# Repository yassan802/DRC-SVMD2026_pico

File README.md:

マイコンにRP2354Aを用いたサーボモータドライバ基板。  
主な従来のものとの変更点はマイコンの変更、チャンネル数が6chになったこと、
リミットスイッチ用端子を新しく付けたこと、サーボ用端子をxhにしたこと。

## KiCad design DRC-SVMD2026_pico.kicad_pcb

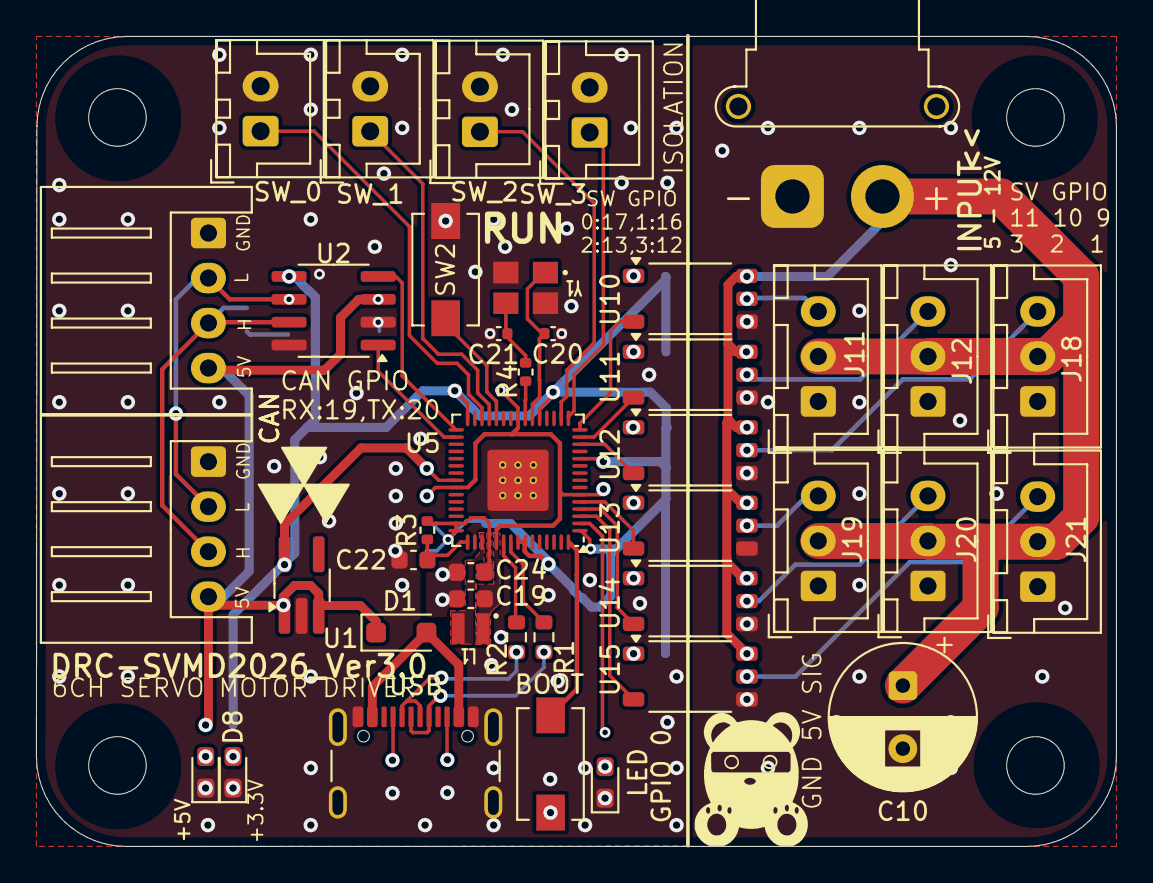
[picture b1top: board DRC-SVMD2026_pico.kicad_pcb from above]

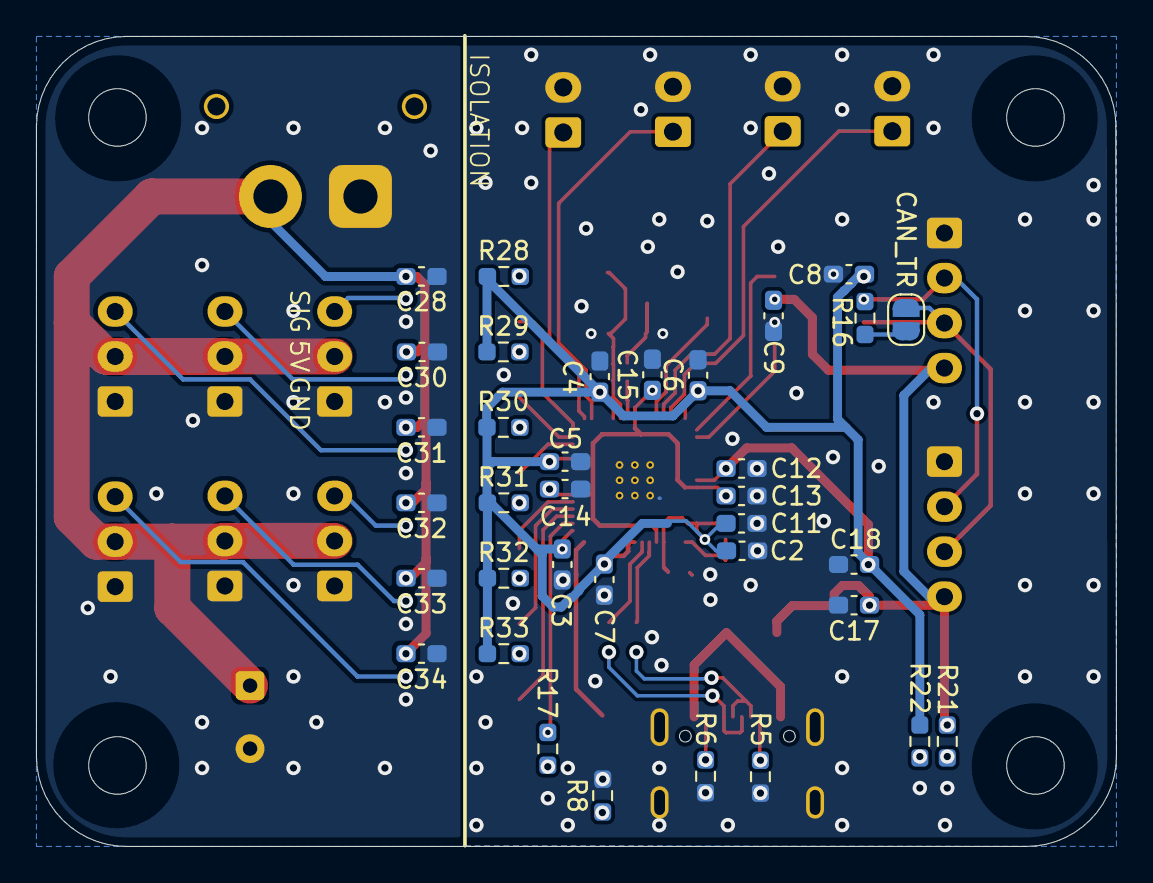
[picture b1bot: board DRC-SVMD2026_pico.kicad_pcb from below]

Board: 2 copper layers, 60.0 x 45.0 mm, 76 parts (35 on the bottom side), 52 nets.

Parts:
C2, C3, C4, C5, C6, C7, C11, C12, C13, C14, C15: 100nF; C_0603_1608Metric_Pad1.08x0.95mm_HandSolder
C8, C9, C28, C30, C31, C32, C33, C34: 0.1u; C_0603_1608Metric_Pad1.08x0.95mm_HandSolder
C10: 220u; CP_Radial_D8.0mm_P3.50mm
C17, C18: 1uF; C_0603_1608Metric_Pad1.08x0.95mm_HandSolder
C19, C22, C24: 4.7uF; C_0603_1608Metric
C20, C21: 15p; C_0402_1005Metric
D1: SS2040FL; D_SOD-123F
D3: LED; LED_0603_1608Metric_Pad1.05x0.95mm_HandSolder
D7: +5V; LED_0603_1608Metric_Pad1.05x0.95mm_HandSolder
D8: +3.3V; LED_0603_1608Metric_Pad1.05x0.95mm_HandSolder
J1: USB; USB_C_Receptacle_GCT_USB4105-xx-A_16P_TopMnt_Horizontal
J7, J8: CAN; JST_XH_S4B-XH-A_1x04_P2.50mm_Horizontal
J9: +5V; AMASS_XT30PW-F_1x02_P2.50mm_Horizontal
J11: SV0; JST_XH_B3B-XH-A_1x03_P2.50mm_Vertical
J12: SV1; JST_XH_B3B-XH-A_1x03_P2.50mm_Vertical
J18: SV2; JST_XH_B3B-XH-A_1x03_P2.50mm_Vertical
J19: SV3; JST_XH_B3B-XH-A_1x03_P2.50mm_Vertical
J20: SV4; JST_XH_B3B-XH-A_1x03_P2.50mm_Vertical
J21: SV5; JST_XH_B3B-XH-A_1x03_P2.50mm_Vertical
JP2: CAN_TR; SolderJumper-2_P1.3mm_Open_RoundedPad1.0x1.5mm
L1: 3.3uH; abracon_aota-b201610s3r3-101-t
R1, R2: 27R; R_0603_1608Metric
R3: 33R; R_0402_1005Metric
R4: 1k; R_0402_1005Metric
R5, R6: 5.1k; R_0603_1608Metric_Pad0.98x0.95mm_HandSolder
R8, R17, R21, R22: 1k; R_0603_1608Metric_Pad0.98x0.95mm_HandSolder
R16: 120; R_0603_1608Metric_Pad0.98x0.95mm_HandSolder
R28, R29, R30, R31, R32, R33: 330; R_0603_1608Metric_Pad0.98x0.95mm_HandSolder
SW1: BOOT; SW_SPST_EVQPE1
SW2: RESET; SW_SPST_EVQPE1
SW_0: 0; JST_XH_B2B-XH-A_1x02_P2.50mm_Vertical
SW_1: 1; JST_XH_B2B-XH-A_1x02_P2.50mm_Vertical
SW_2: 2; JST_XH_B2B-XH-A_1x02_P2.50mm_Vertical
SW_3: 3; JST_XH_B2B-XH-A_1x02_P2.50mm_Vertical
U1: RT9080-33GJ5; TSOT-23-5_HandSoldering
U2: ata6561-gaqw-n; SOIC-8_3.9x4.9mm_P1.27mm
U5: RP2350A; QFN-60-1EP_7x7mm_P0.4mm_EP3.4x3.4mm_ThermalVias
U10, U11, U12, U13, U14, U15: TLP2361; SO-5-6_4.55x3.7mm_P1.27mm
Y1: 12MHz_ABM8-272-T3; generic_xtalcc320x250x80-4

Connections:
+1.1V: C13.1, C14.1, C15.1, C19.1, L1.1, U5.6 (DVDD), U5.23 (DVDD), U5.39 (DVDD), U5.50 (VREG_FB)
+3.3V: C2.1, C3.1, C4.1, C5.1, C6.1, C7.1, C8.2, C11.1, C12.1, C18.1, C24.1, R3.2, R22.1, R28.1, R29.1, R30.1, R31.1, R32.1, R33.1, U1.5 (VOUT), U2.5 (Vio), U5.1 (IOVDD), U5.11 (IOVDD), U5.20 (IOVDD), U5.30 (IOVDD), U5.38 (IOVDD), U5.44 (ADC_AVDD), U5.45 (IOVDD), U5.49 (VREG_VIN), U5.53 (USB_OTP_VDD), U5.54 (QSPI_IOVDD)
+5V: C9.2, C17.1, D1.1 (K), J7.4, J8.4, R21.1, U1.1 (VIN), U1.3 (EN), U2.3 (VDD)
+5VP: C10.1, C28.2, C30.2, C31.2, C32.2, C33.2, C34.2, J9.2, J11.2, J12.2, J18.2, J19.2, J20.2, J21.2, U10.6 (VDD), U11.6 (VDD), U12.6 (VDD), U13.6 (VDD), U14.6 (VDD), U15.6 (VDD)
CAN_H: J7.3, J8.3, JP2.2 (B), U2.7 (CANH)
CAN_L: J7.2, J8.2, R16.2, U2.6 (CANL)
CAN_RX: U2.4 (RXD), U5.31 (GPIO19)
CAN_TX: U2.1 (TXD), U5.32 (GPIO20)
GND: C2.2, C3.2, C4.2, C5.2, C6.2, C7.2, C8.1, C9.1, C11.2, C12.2, C13.2, C14.2, C15.2, C17.2, C18.2, C19.2, C20.2, C21.2, C22.2, C24.2, D3.1 (K), D7.1 (K), D8.1 (K), J1.A1 (GND), J1.A12 (GND), J1.B1 (GND), J1.B12 (GND), J1.S1 (SHIELD), J7.1, J8.1, R5.2, R6.2, R8.2, SW2.1, SW_0.2, SW_1.2, SW_2.2, SW_3.2, U1.2 (GND), U2.2 (VSS), U2.8 (STBY), U5.47 (VREG_PGND), U5.61 (GND), Y1.2, Y1.4
GNDPWR: C10.2, C28.1, C30.1, C31.1, C32.1, C33.1, C34.1, J9.1, J11.1, J12.1, J18.1, J19.1, J20.1, J21.1, U10.4 (GND), U11.4 (GND), U12.4 (GND), U13.4 (GND), U14.4 (GND), U15.4 (GND)
LED: R17.1, U5.2 (GPIO0)
unnamed: C21.1, R4.2, Y1.3
unnamed: D1.2 (A), J1.A4 (VBUS), J1.A9 (VBUS), J1.B4 (VBUS), J1.B9 (VBUS)
unnamed: D3.2 (A), R17.2
unnamed: D7.2 (A), R21.2
unnamed: D8.2 (A), R22.2
unnamed: J1.A5 (CC1), R5.1
unnamed: J1.B5 (CC2), R6.1
unnamed: J11.3, U10.5 (VO)
unnamed: J12.3, U11.5 (VO)
unnamed: J18.3, U12.5 (VO)
unnamed: J19.3, U13.5 (VO)
unnamed: J20.3, U14.5 (VO)
unnamed: J21.3, U15.5 (VO)
unnamed: JP2.1 (A), R16.1
unnamed: R8.1, SW1.1
unnamed: SW1.2, U5.60 (QSPI_SS)
unnamed: SW2.2, U5.26 (RUN)
unnamed: R2.2, U5.51 (USB_DM)
unnamed: R1.2, U5.52 (USB_DP)
unnamed: C22.1, R3.1, U5.46 (VREG_AVDD)
unnamed: L1.2, U5.48 (VREG_LX)
unnamed: C20.1, U5.21 (XIN), Y1.1
unnamed: R4.1, U5.22 (XOUT)
unnamed: R28.2, U10.1 (A)
unnamed: R29.2, U11.1 (A)
unnamed: R30.2, U12.1 (A)
unnamed: R31.2, U13.1 (A)
unnamed: R32.2, U14.1 (A)
unnamed: R33.2, U15.1 (A)
SV0: U5.15 (GPIO11), U10.3 (K)
SV1: U5.14 (GPIO10), U11.3 (K)
SV2: U5.13 (GPIO9), U12.3 (K)
SV3: U5.5 (GPIO3), U13.3 (K)
SV4: U5.4 (GPIO2), U14.3 (K)
SV5: U5.3 (GPIO1), U15.3 (K)
SW0: SW_0.1, U5.28 (GPIO17)
SW1: SW_1.1, U5.27 (GPIO16)
SW2: SW_2.1, U5.17 (GPIO13)
SW3: SW_3.1, U5.16 (GPIO12)
USB_D_N: J1.A7 (D-), J1.B7 (D-), R2.1
USB_D_P: J1.A6 (D+), J1.B6 (D+), R1.1
